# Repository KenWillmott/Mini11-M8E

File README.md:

# Mini11-M8E
MC68HC11A1 MCU based SBC, no ROM
Please read the wiki https://github.com/KenWillmott/Mini11-M8E/wiki

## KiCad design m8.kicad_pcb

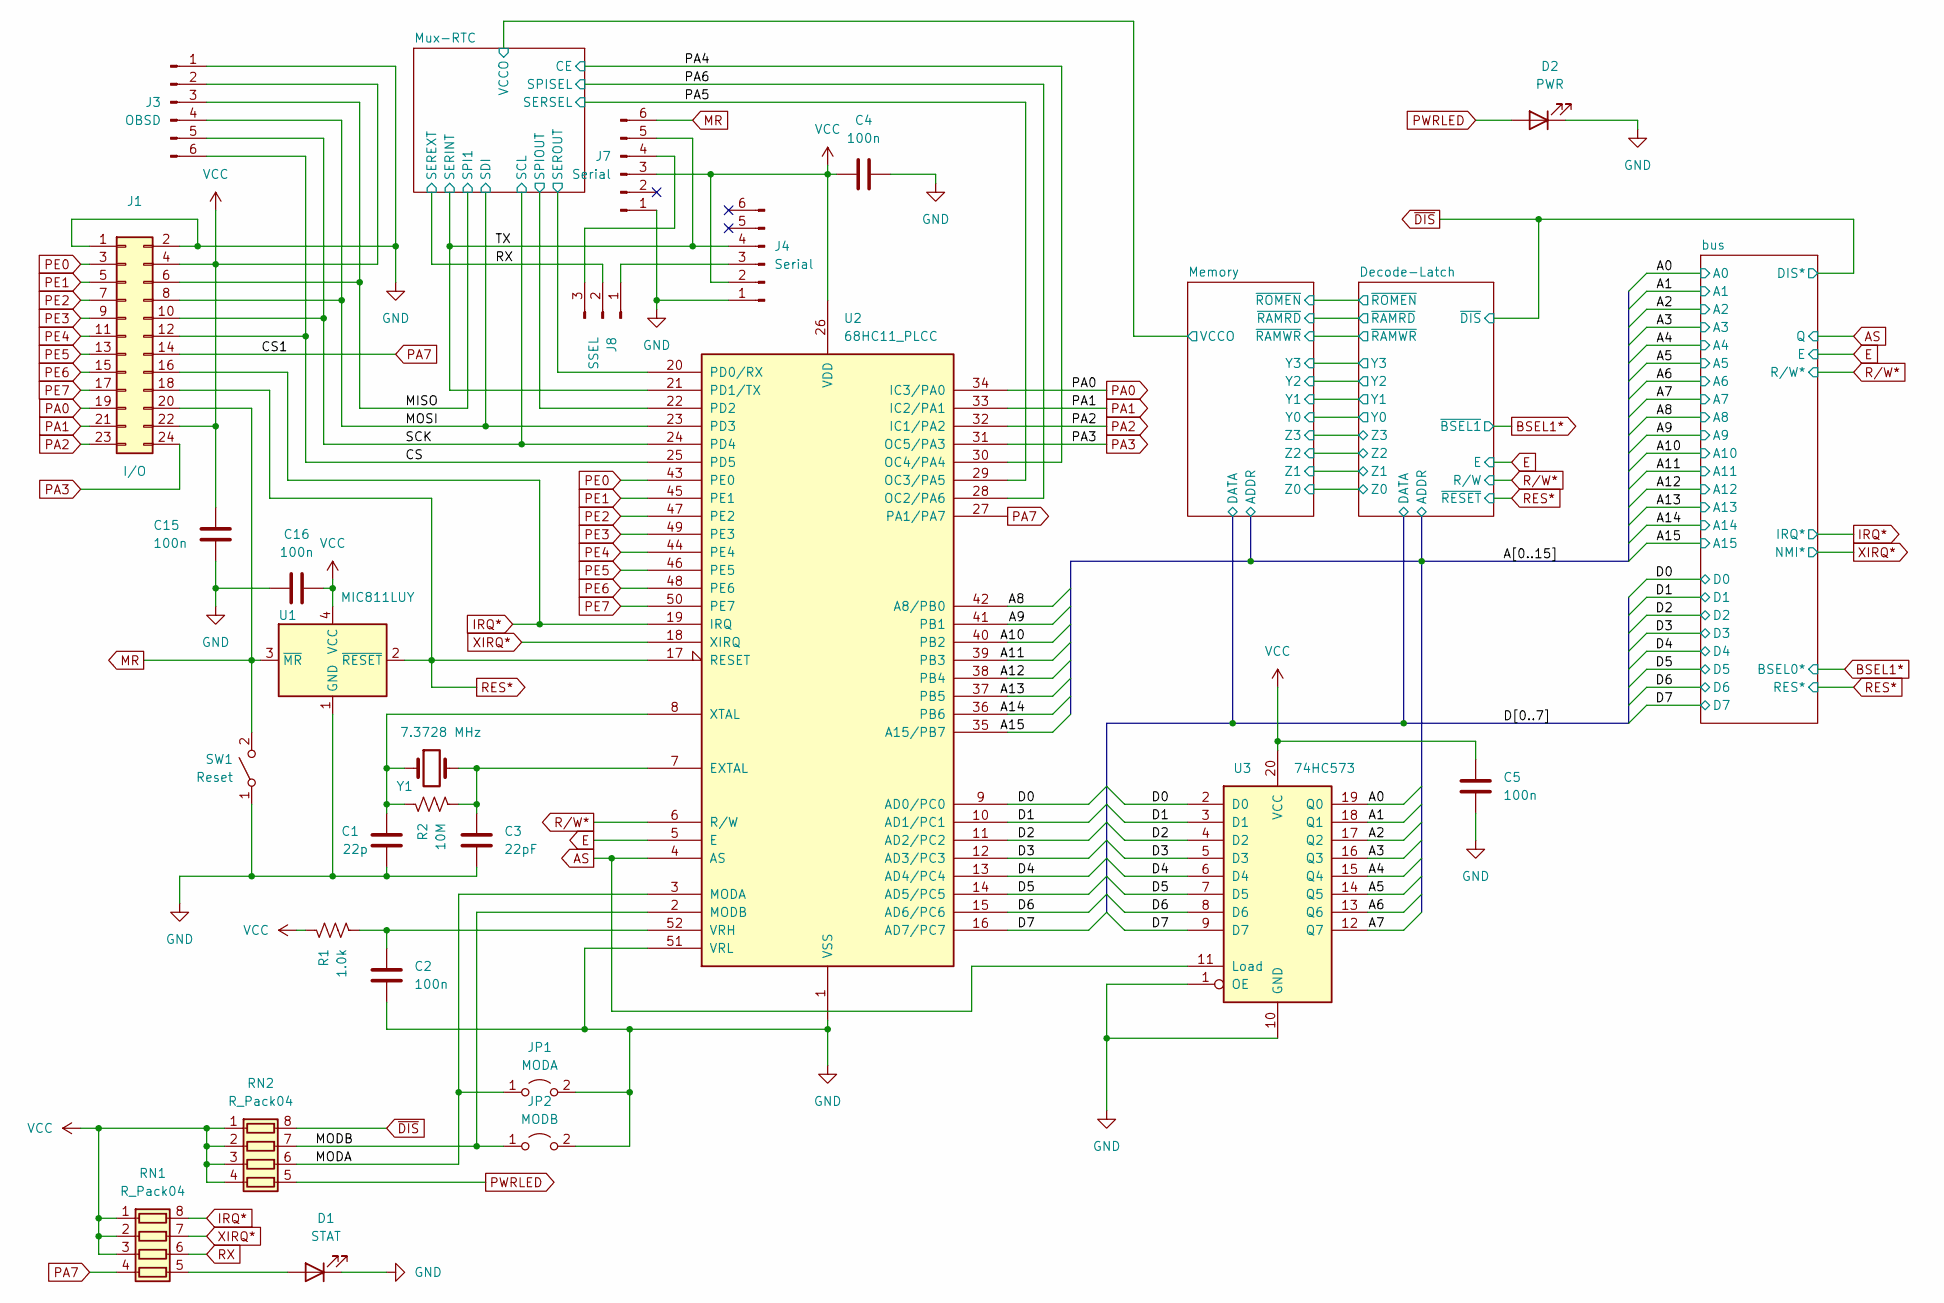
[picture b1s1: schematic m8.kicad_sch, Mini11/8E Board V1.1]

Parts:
C1: 22p; C_0603_1608Metric
C2, C4, C5, C15, C16: 100n; C_0603_1608Metric
C3: 22pF; C_0603_1608Metric
D1: STAT; LED_0603_1608Metric
D2: PWR; LED_0603_1608Metric
J1: I/O; PinHeader_2x12_P2.54mm_Horizontal
J3: OBSD; PinHeader_1x06_P2.54mm_Vertical
J4: Serial; PinHeader_1x06_P2.54mm_Vertical
J7: Serial; PinSocket_1x06_P2.54mm_Vertical
J8: SSEL; PinHeader_1x03_P2.54mm_Vertical
JP1: MODA; PinHeader_1x02_P2.54mm_Vertical
JP2: MODB; PinHeader_1x02_P2.54mm_Vertical
R1: 1.0k; R_0603_1608Metric
R2: 10M; R_0603_1608Metric
RN1, RN2: R_Pack04; R_Array_Convex_4x1206
SW1: Reset; SW_PUSH_6mm_H4.3mm
U1: MIC811LUY; SOT-143
U2: 68HC11_PLCC; PLCC-52_SMD-Socket
U3: 74HC573; SO-20_12.8x7.5mm_P1.27mm
Y1: 7.3728 MHz; Crystal_SMD_FOX_FQ7050-4Pin_7.0x5.0mm

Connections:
/A0: U3.19 (Q0); also elsewhere on the board
/A1: U3.18 (Q1); also elsewhere on the board
/A2: U3.17 (Q2); also elsewhere on the board
/A3: U3.16 (Q3); also elsewhere on the board
/A4: U3.15 (Q4); also elsewhere on the board
/A5: U3.14 (Q5); also elsewhere on the board
/A6: U3.13 (Q6); also elsewhere on the board
/A7: U3.12 (Q7); also elsewhere on the board
/A8: U2.42 (A8/PB0); also elsewhere on the board
/A9: U2.41 (PB1); also elsewhere on the board
/A10: U2.40 (PB2); also elsewhere on the board
/A11: U2.39 (PB3); also elsewhere on the board
/A12: U2.38 (PB4); also elsewhere on the board
/A13: U2.37 (PB5); also elsewhere on the board
/A14: U2.36 (PB6); also elsewhere on the board
/A15: U2.35 (A15/PB7); also elsewhere on the board
/CS: J1.12, J3.6, U2.25 (PD5)
/D0: U2.9 (AD0/PC0), U3.2 (D0); also elsewhere on the board
/D1: U2.10 (AD1/PC1), U3.3 (D1); also elsewhere on the board
/D2: U2.11 (AD2/PC2), U3.4 (D2); also elsewhere on the board
/D3: U2.12 (AD3/PC3), U3.5 (D3); also elsewhere on the board
/D4: U2.13 (AD4/PC4), U3.6 (D4); also elsewhere on the board
/D5: U2.14 (AD5/PC5), U3.7 (D5); also elsewhere on the board
/D6: U2.15 (AD6/PC6), U3.8 (D6); also elsewhere on the board
/D7: U2.16 (AD7/PC7), U3.9 (D7); also elsewhere on the board
/MISO: J1.6, J3.3; also elsewhere on the board
/MODA: JP1.1 (A), RN2.6 (R3.2), U2.3 (MODA)
/MODB: JP2.1 (A), RN2.7 (R2.2), U2.2 (MODB)
/MOSI: J1.8, J3.4, U2.23 (PD3); also elsewhere on the board
/Mux-RTC/SEROUT: U2.20 (PD0/RX); also elsewhere on the board
/Mux-RTC/SPIOUT: U2.22 (PD2); also elsewhere on the board
/PA4: U2.30 (OC4/PA4); also elsewhere on the board
/PA5: U2.29 (OC3/PA5); also elsewhere on the board
/PA6: U2.28 (OC2/PA6); also elsewhere on the board
/SCK: J1.10, J3.5, U2.24 (PD4); also elsewhere on the board
/TX: J4.4, J7.5, U2.21 (PD1/TX); also elsewhere on the board
AS: U2.4 (AS), U3.11 (Load); also elsewhere on the board
E: U2.5 (E); also elsewhere on the board
GND: C1.2, C2.2, C3.2, C4.2, C5.2, C15.2, C16.1, D1.1 (K), D2.1 (K), J1.1, J1.2, J3.1, J4.1, J7.1, JP1.2 (B), JP2.2 (B), SW1.1 (A), U1.1 (GND), U2.1 (VSS), U2.51 (VRL), U3.1 (OE), U3.10 (GND); also elsewhere on the board
IRQ*: J1.16, RN1.8 (R1.2), U2.19 (IRQ); also elsewhere on the board
MR: J1.20, J7.6, SW1.2 (B), U1.3 (~MR)
unnamed: D1.2 (A), RN1.5 (R4.2)
unnamed: J4.3, J8.1
unnamed: J7.4, J8.3
unnamed: C3.1, R2.2, U2.7 (EXTAL), Y1.3
unnamed: C2.1, R1.2, U2.52 (VRH)
unnamed: C1.1, R2.1, U2.8 (XTAL), Y1.1
PA0: J1.19, U2.34 (IC3/PA0)
PA1: J1.21, U2.33 (IC2/PA1)
PA2: J1.23, U2.32 (IC1/PA2)
PA3: J1.24, U2.31 (OC5/PA3)
PA7: J1.14, RN1.4 (R4.1), U2.27 (PA1/PA7)
PE0: J1.3, U2.43 (PE0)
PE1: J1.5, U2.45 (PE1)
PE2: J1.7, U2.47 (PE2)
PE3: J1.9, U2.49 (PE3)
PE4: J1.11, U2.44 (PE4)
PE5: J1.13, U2.46 (PE5)
PE6: J1.15, U2.48 (PE6)
PE7: J1.17, U2.50 (PE7)
PWRLED: D2.2 (A), RN2.5 (R4.2)
RES*: J1.18, U1.2 (~RESET), U2.17 (RESET); also elsewhere on the board
RX: J8.2, RN1.6 (R3.2); also elsewhere on the board
R/W*: U2.6 (R/W); also elsewhere on the board
VCC: C4.1, C5.1, C15.1, C16.2, J1.4, J1.22, J3.2, J4.2, J7.3, R1.1, RN1.1 (R1.1), RN1.2 (R2.1), RN1.3 (R3.1), RN2.1 (R1.1), RN2.2 (R2.1), RN2.3 (R3.1), RN2.4 (R4.1), U1.4 (VCC), U2.26 (VDD), U3.20 (VCC); also elsewhere on the board
XIRQ*: RN1.7 (R2.2), U2.18 (XIRQ); also elsewhere on the board
~DIS: RN2.8 (R1.2); also elsewhere on the board

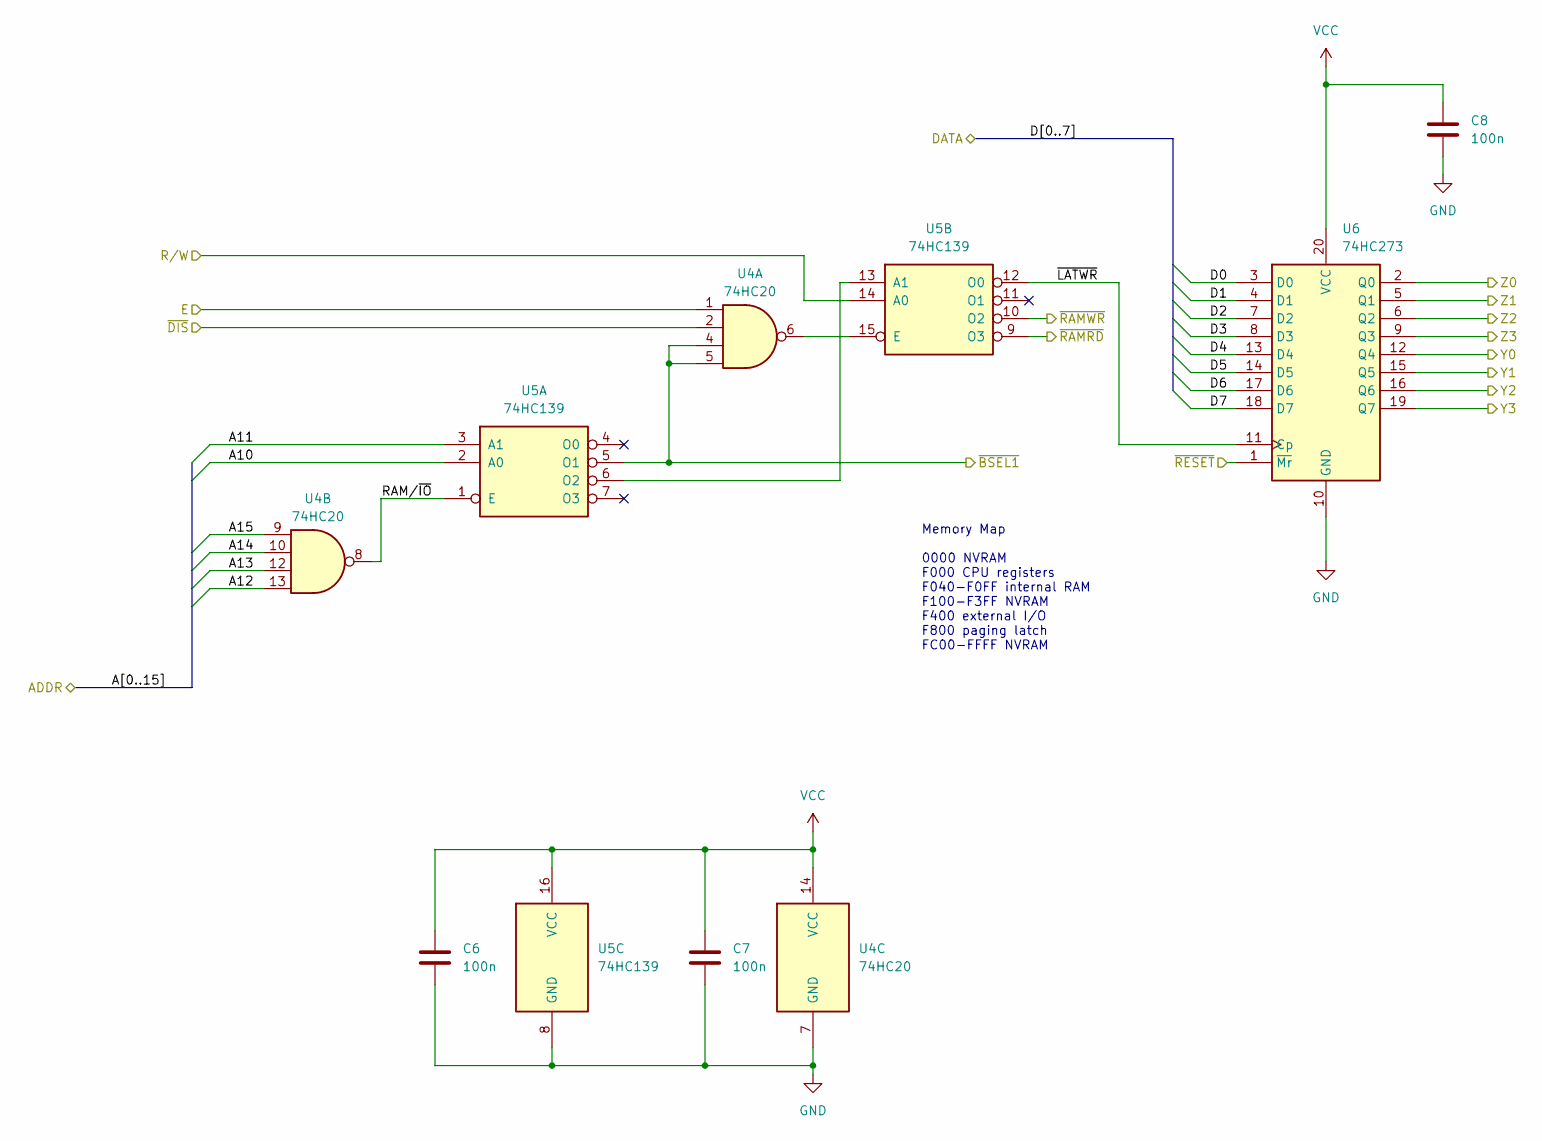
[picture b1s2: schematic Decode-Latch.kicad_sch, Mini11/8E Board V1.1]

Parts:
C6, C7, C8: 100n; C_0603_1608Metric
U4: 74HC20; SO-14_3.9x8.65mm_P1.27mm
U5: 74HC139; SO-16_3.9x9.9mm_P1.27mm
U6: 74HC273; SOP-20_7.5x12.8mm_P1.27mm

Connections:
/A10: U5.2 (A0); also elsewhere on the board
/A11: U5.3 (A1); also elsewhere on the board
/A12: U4.13; also elsewhere on the board
/A13: U4.12; also elsewhere on the board
/A14: U4.10; also elsewhere on the board
/A15: U4.9; also elsewhere on the board
/D0: U6.3 (D0); also elsewhere on the board
/D1: U6.4 (D1); also elsewhere on the board
/D2: U6.7 (D2); also elsewhere on the board
/D3: U6.8 (D3); also elsewhere on the board
/D4: U6.13 (D4); also elsewhere on the board
/D5: U6.14 (D5); also elsewhere on the board
/D6: U6.17 (D6); also elsewhere on the board
/D7: U6.18 (D7); also elsewhere on the board
/Decode-Latch/RAM/~IO: U4.8, U5.1 (E)
/Decode-Latch/Y0: U6.12 (Q4); also elsewhere on the board
/Decode-Latch/Y1: U6.15 (Q5); also elsewhere on the board
/Decode-Latch/Y2: U6.16 (Q6); also elsewhere on the board
/Decode-Latch/Y3: U6.19 (Q7); also elsewhere on the board
/Decode-Latch/Z0: U6.2 (Q0); also elsewhere on the board
/Decode-Latch/Z1: U6.5 (Q1); also elsewhere on the board
/Decode-Latch/Z2: U6.6 (Q2); also elsewhere on the board
/Decode-Latch/Z3: U6.9 (Q3); also elsewhere on the board
/Decode-Latch/~LATWR: U5.12 (O0), U6.11 (Cp)
/Decode-Latch/~RAMRD: U5.9 (O3); also elsewhere on the board
/Decode-Latch/~RAMWR: U5.10 (O2); also elsewhere on the board
BSEL1*: U4.4, U4.5, U5.5 (O1); also elsewhere on the board
E: U4.1; also elsewhere on the board
GND: C6.2, C7.2, C8.2, U4.7 (GND), U5.8 (GND), U6.10 (GND); also elsewhere on the board
unnamed: U5.6 (O2), U5.13 (A1)
unnamed: U4.6, U5.15 (E)
RES*: U6.1 (~Mr); also elsewhere on the board
R/W*: U5.14 (A0); also elsewhere on the board
VCC: C6.1, C7.1, C8.1, U4.14 (VCC), U5.16 (VCC), U6.20 (VCC); also elsewhere on the board
~DIS: U4.2; also elsewhere on the board

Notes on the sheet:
Memory Map 0000 NVRAM F000 CPU registers F040-F0FF internal RAM F100-F3FF NVRAM F400 external I/O F800 paging latch FC00-FFFF NVRAM

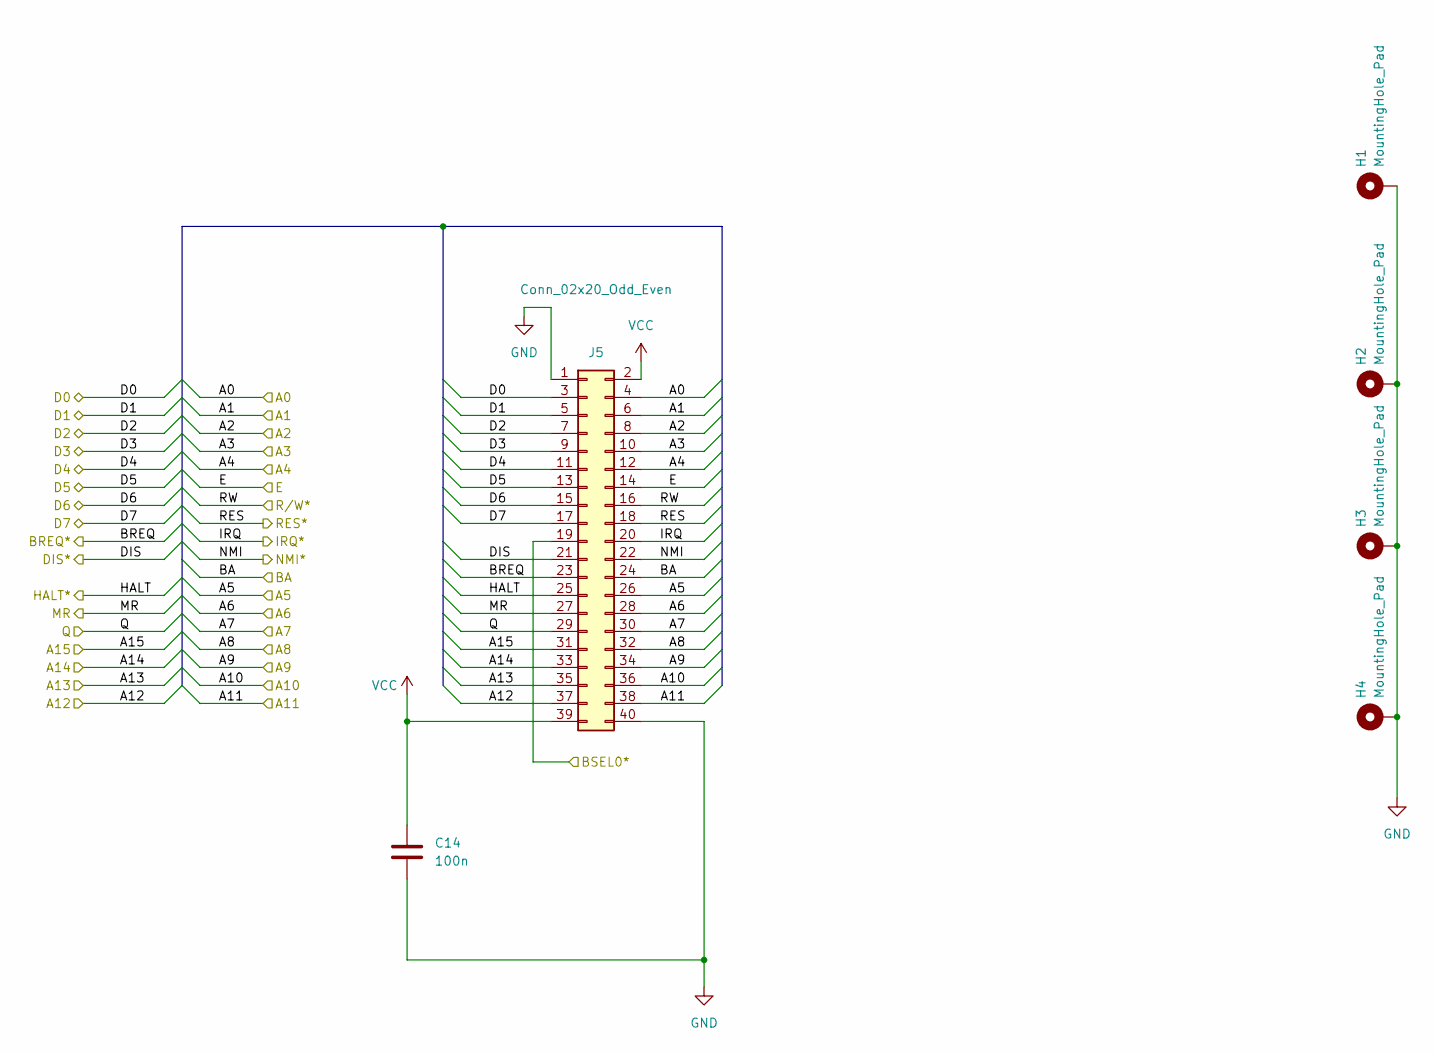
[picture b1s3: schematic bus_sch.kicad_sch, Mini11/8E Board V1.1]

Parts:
C14: 100n; C_0603_1608Metric
H1, H2, H3, H4: MountingHole_Pad; MountingHole_3.2mm_M3_Pad
J5: Conn_02x20_Odd_Even; PinSocket_2x20_P2.54mm_Vertical

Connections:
/A0: J5.4; also elsewhere on the board
/A1: J5.6; also elsewhere on the board
/A2: J5.8; also elsewhere on the board
/A3: J5.10; also elsewhere on the board
/A4: J5.12; also elsewhere on the board
/A5: J5.26; also elsewhere on the board
/A6: J5.28; also elsewhere on the board
/A7: J5.30; also elsewhere on the board
/A8: J5.32; also elsewhere on the board
/A9: J5.34; also elsewhere on the board
/A10: J5.36; also elsewhere on the board
/A11: J5.38; also elsewhere on the board
/A12: J5.37; also elsewhere on the board
/A13: J5.35; also elsewhere on the board
/A14: J5.33; also elsewhere on the board
/A15: J5.31; also elsewhere on the board
/D0: J5.3; also elsewhere on the board
/D1: J5.5; also elsewhere on the board
/D2: J5.7; also elsewhere on the board
/D3: J5.9; also elsewhere on the board
/D4: J5.11; also elsewhere on the board
/D5: J5.13; also elsewhere on the board
/D6: J5.15; also elsewhere on the board
/D7: J5.17; also elsewhere on the board
/bus/BA: J5.24
/bus/BREQ: J5.23
/bus/HALT: J5.25
/bus/MR: J5.27
AS: J5.29; also elsewhere on the board
BSEL1*: J5.19; also elsewhere on the board
E: J5.14; also elsewhere on the board
GND: C14.1, H1.1, H2.1, H3.1, H4.1, J5.1, J5.40; also elsewhere on the board
IRQ*: J5.20; also elsewhere on the board
RES*: J5.18; also elsewhere on the board
R/W*: J5.16; also elsewhere on the board
VCC: C14.2, J5.2, J5.39; also elsewhere on the board
XIRQ*: J5.22; also elsewhere on the board
~DIS: J5.21; also elsewhere on the board

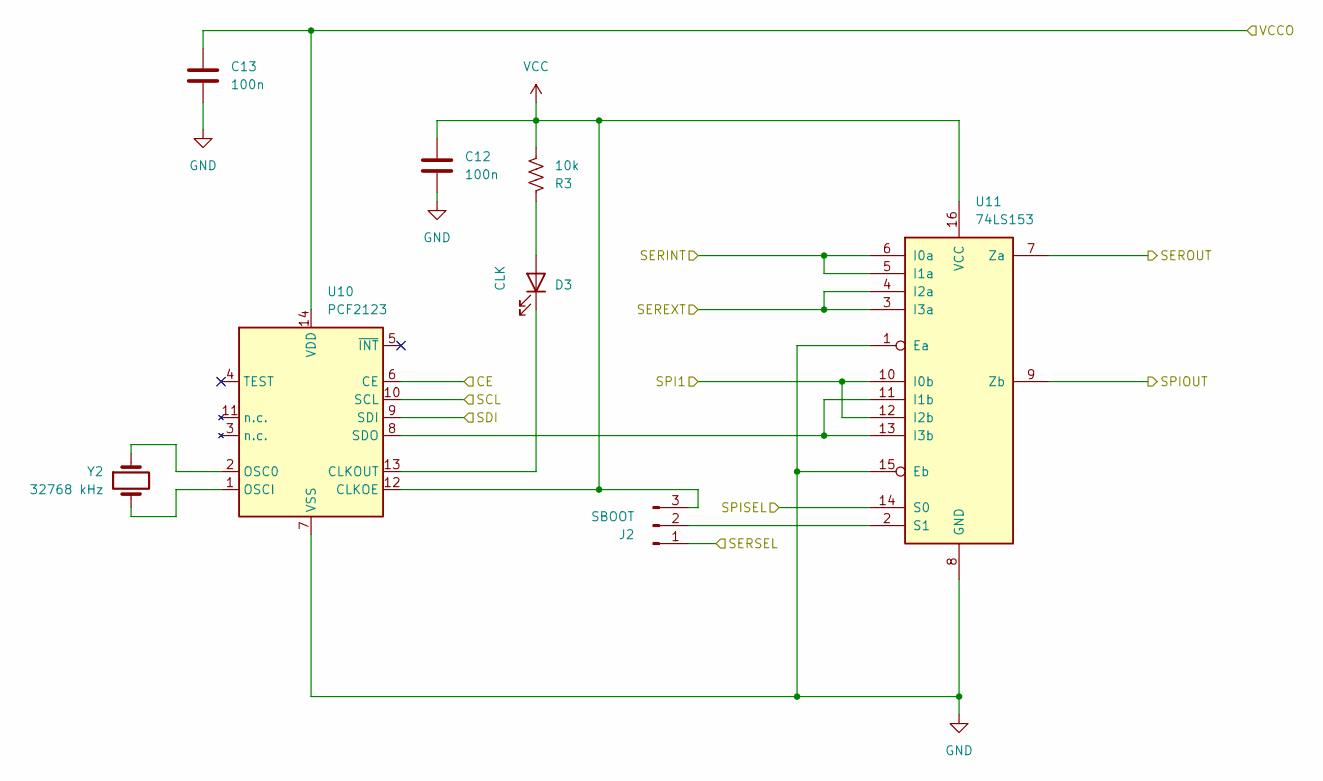
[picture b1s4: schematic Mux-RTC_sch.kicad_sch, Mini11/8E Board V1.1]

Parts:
C12, C13: 100n; C_0603_1608Metric
D3: CLK; LED_0603_1608Metric
J2: SBOOT; PinHeader_1x03_P2.54mm_Vertical
R3: 10k; R_0603_1608Metric
U10: PCF2123; TSSOP-14_4.4x5mm_P0.65mm
U11: 74LS153; SOIC-16_3.9x9.9mm_P1.27mm
Y2: 32768 kHz; Crystal_SMD_2012-2Pin_2.0x1.2mm

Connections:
/MISO: U11.10 (I0b), U11.12 (I2b); also elsewhere on the board
/MOSI: U10.9 (SDI); also elsewhere on the board
/Memory/VCCO: C13.2, U10.14 (VDD); also elsewhere on the board
/Mux-RTC/SEROUT: U11.7 (Za); also elsewhere on the board
/Mux-RTC/SPIOUT: U11.9 (Zb); also elsewhere on the board
/PA4: U10.6 (CE); also elsewhere on the board
/PA5: J2.1; also elsewhere on the board
/PA6: U11.14 (S0); also elsewhere on the board
/SCK: U10.10 (SCL); also elsewhere on the board
/TX: U11.5 (I1a), U11.6 (I0a); also elsewhere on the board
GND: C12.2, C13.1, U10.7 (VSS), U11.1 (Ea), U11.8 (GND), U11.15 (Eb); also elsewhere on the board
unnamed: D3.2 (A), R3.1
unnamed: D3.1 (K), U10.13 (CLKOUT)
unnamed: J2.2, U11.2 (S1)
unnamed: U10.2 (OSC0), Y2.1
unnamed: U10.1 (OSCI), Y2.2
unnamed: U10.8 (SDO), U11.11 (I1b), U11.13 (I3b)
RX: U11.3 (I3a), U11.4 (I2a); also elsewhere on the board
VCC: C12.1, J2.3, R3.2, U10.12 (CLKOE), U11.16 (VCC); also elsewhere on the board

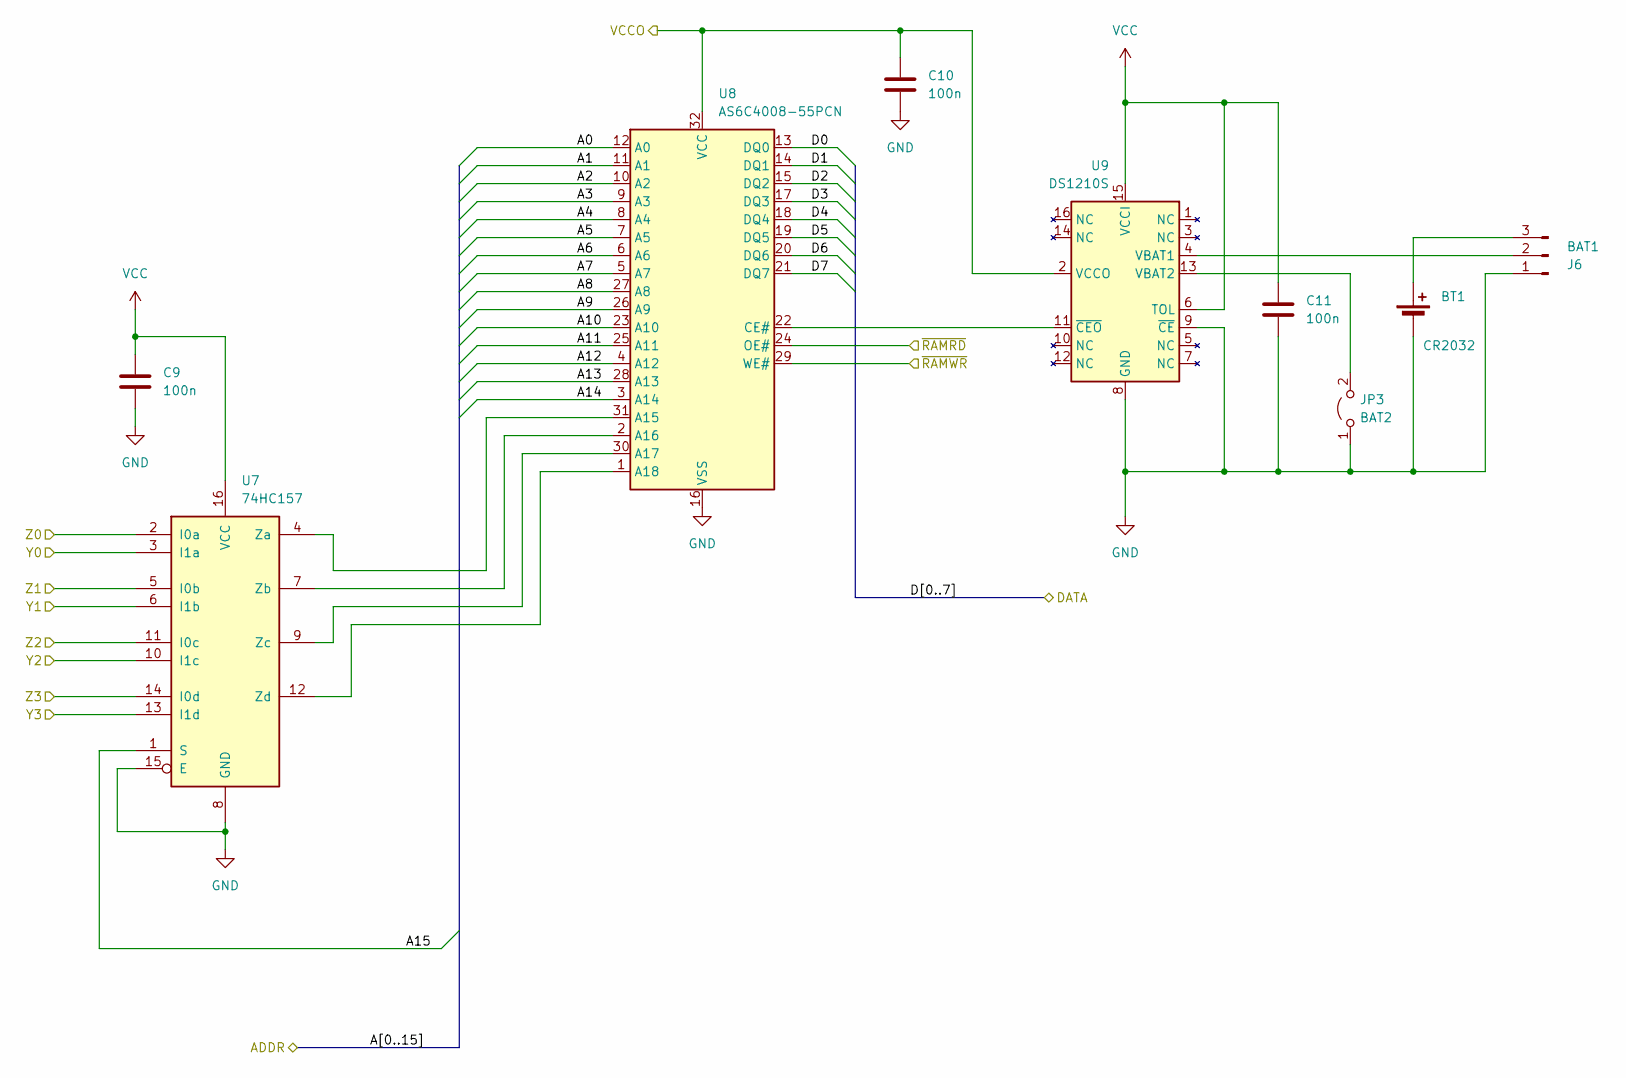
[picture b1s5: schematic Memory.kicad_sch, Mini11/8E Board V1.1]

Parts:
BT1: CR2032; BatteryHolder_Keystone_107_1x23mm
C9, C10, C11: 100n; C_0603_1608Metric
J6: BAT1; PinHeader_1x03_P2.54mm_Vertical
JP3: BAT2; PinHeader_1x02_P2.54mm_Vertical
U7: 74HC157; SO-16_3.9x9.9mm_P1.27mm
U8: AS6C4008-55PCN; SSOP-32_11.305x20.495mm_P1.27mm
U9: DS1210S; SOIC-16W_7.5x10.3mm_P1.27mm

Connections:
/A0: U8.12 (A0); also elsewhere on the board
/A1: U8.11 (A1); also elsewhere on the board
/A2: U8.10 (A2); also elsewhere on the board
/A3: U8.9 (A3); also elsewhere on the board
/A4: U8.8 (A4); also elsewhere on the board
/A5: U8.7 (A5); also elsewhere on the board
/A6: U8.6 (A6); also elsewhere on the board
/A7: U8.5 (A7); also elsewhere on the board
/A8: U8.27 (A8); also elsewhere on the board
/A9: U8.26 (A9); also elsewhere on the board
/A10: U8.23 (A10); also elsewhere on the board
/A11: U8.25 (A11); also elsewhere on the board
/A12: U8.4 (A12); also elsewhere on the board
/A13: U8.28 (A13); also elsewhere on the board
/A14: U8.3 (A14); also elsewhere on the board
/A15: U7.1 (S); also elsewhere on the board
/D0: U8.13 (DQ0); also elsewhere on the board
/D1: U8.14 (DQ1); also elsewhere on the board
/D2: U8.15 (DQ2); also elsewhere on the board
/D3: U8.17 (DQ3); also elsewhere on the board
/D4: U8.18 (DQ4); also elsewhere on the board
/D5: U8.19 (DQ5); also elsewhere on the board
/D6: U8.20 (DQ6); also elsewhere on the board
/D7: U8.21 (DQ7); also elsewhere on the board
/Decode-Latch/Y0: U7.3 (I1a); also elsewhere on the board
/Decode-Latch/Y1: U7.6 (I1b); also elsewhere on the board
/Decode-Latch/Y2: U7.10 (I1c); also elsewhere on the board
/Decode-Latch/Y3: U7.13 (I1d); also elsewhere on the board
/Decode-Latch/Z0: U7.2 (I0a); also elsewhere on the board
/Decode-Latch/Z1: U7.5 (I0b); also elsewhere on the board
/Decode-Latch/Z2: U7.11 (I0c); also elsewhere on the board
/Decode-Latch/Z3: U7.14 (I0d); also elsewhere on the board
/Decode-Latch/~RAMRD: U8.24 (OE#); also elsewhere on the board
/Decode-Latch/~RAMWR: U8.29 (WE#); also elsewhere on the board
/Memory/VCCO: C10.1, U8.32 (VCC), U9.2 (VCCO); also elsewhere on the board
GND: BT1.2 (-), C9.2, C10.2, C11.2, J6.1, JP3.1 (A), U7.8 (GND), U7.15 (E), U8.16 (VSS), U9.8 (GND), U9.9 (~CE); also elsewhere on the board
unnamed: BT1.1 (+), J6.3
unnamed: J6.2, U9.4 (VBAT1)
unnamed: JP3.2 (B), U9.13 (VBAT2)
unnamed: U7.4 (Za), U8.31 (A15)
unnamed: U7.7 (Zb), U8.2 (A16)
unnamed: U7.9 (Zc), U8.30 (A17)
unnamed: U7.12 (Zd), U8.1 (A18)
unnamed: U8.22 (CE#), U9.11 (~CEO)
VCC: C9.1, C11.1, U7.16 (VCC), U9.6 (TOL), U9.15 (VCCI); also elsewhere on the board

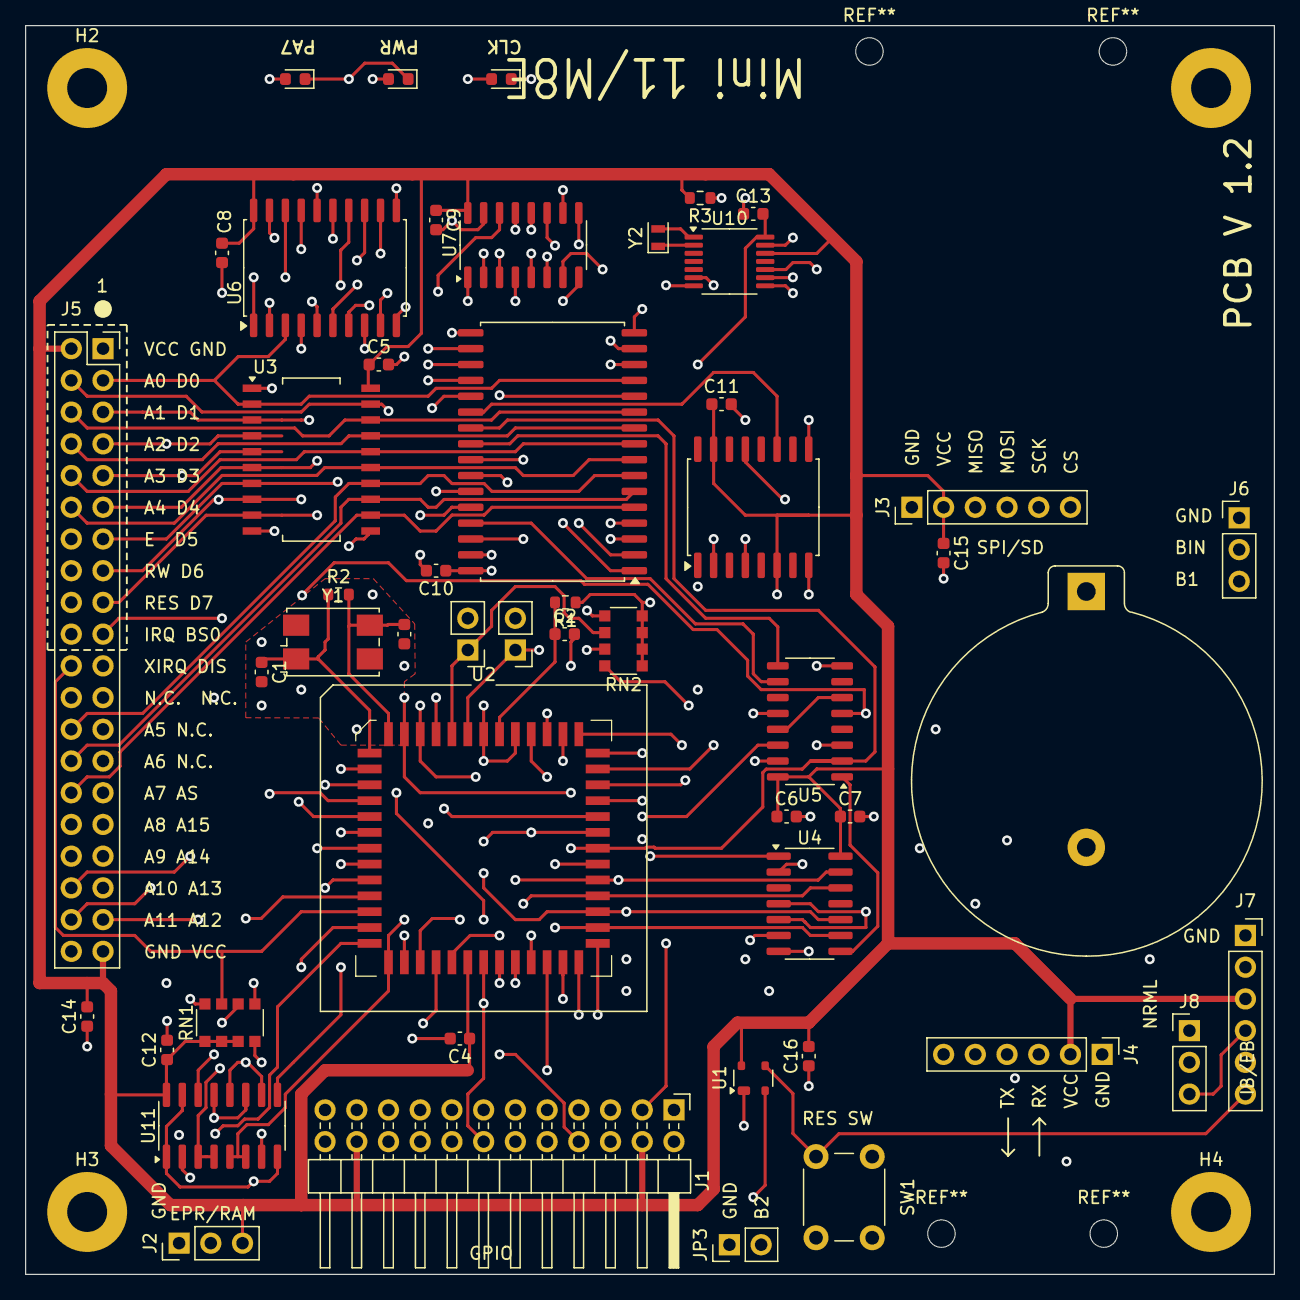
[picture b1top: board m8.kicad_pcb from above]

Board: 4 copper layers, 100.0 x 100.0 mm, 54 parts (0 on the bottom side), 97 nets.

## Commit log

2024-10-31 initial
2024-10-31 Bill of Materials
2024-11-01 completed board image
2024-11-03 preliminary firmware RAM boot only
2024-11-04 bug fix
2024-11-04 adding monitor source code
2024-11-19 EEPROM resident boot and monitor
2024-11-20 Add files via upload
    EEPROM resident boot + monitor
2024-11-20 Add files via upload
    MCU specific definitions
2024-11-20 Add files via upload
    EEPROM boot + monitor source
2024-12-31 kbug monitor as bootable disk image
2024-12-31 burn to SD
2024-12-31 EEPROM resident boot code
2024-12-31 install in EEPROM using debug connection
